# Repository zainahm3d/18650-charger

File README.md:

# 18650-charger
Dual channel USB-C LiFeP04 18650 charger based on 2x LTC4121 with two independant channels. Fully charged voltage is set to 3.6V at a current of 400mA.

## Images

## Test results from charging two cells
Capture from a Saleae logic analyzer. See the data file [here](doc/chargetest.sal)

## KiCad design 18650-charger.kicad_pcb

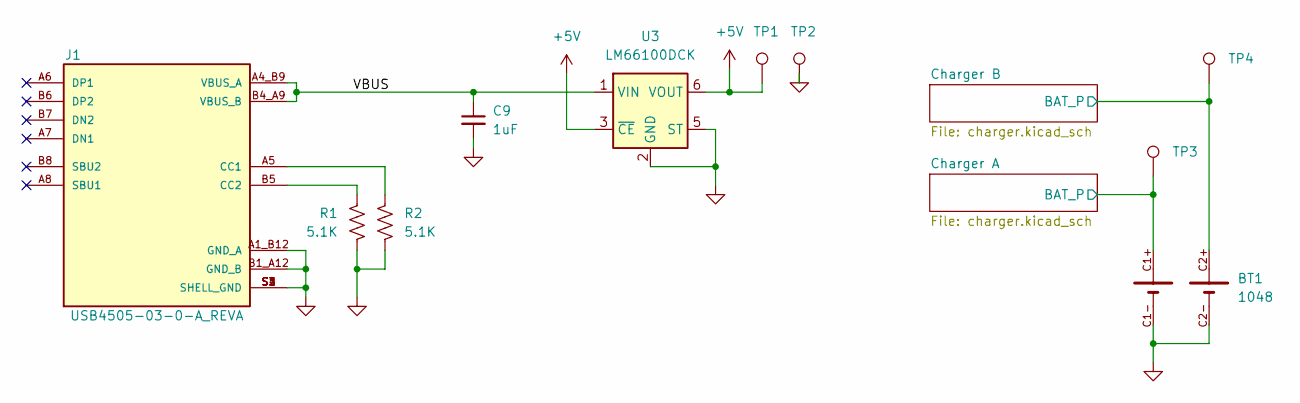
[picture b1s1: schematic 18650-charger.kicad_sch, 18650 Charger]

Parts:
BT1: 1048; BAT_1048
C9: 1uF; C_0402_1005Metric
J1: USB4505-03-0-A_REVA; GCT_USB4505-03-0-A_REVA; PARTREV A
R1, R2: 5.1K; R_0402_1005Metric
TP1, TP2, TP3, TP4: TestPoint; TP+195X110
U3: LM66100DCK; SOT-363_SC-70-6

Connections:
+5V: TP1.1, U3.3 (~CE), U3.6 (VOUT); also elsewhere on the board
/Charger A/BAT_P: BT1.C1+, TP3.1; also elsewhere on the board
/Charger B/BAT_P: BT1.C2+, TP4.1; also elsewhere on the board
/VBUS: C9.1, J1.A4_B9 (VBUS_A), J1.B4_A9 (VBUS_B), U3.1 (VIN)
GND: BT1.C1-, BT1.C2-, C9.2, J1.A1_B12 (GND_A), J1.B1_A12 (GND_B), J1.S1 (SHELL_GND), J1.S2 (SHELL_GND), J1.S3 (SHELL_GND), J1.S4 (SHELL_GND), R1.1, R2.2, TP2.1, U3.2 (GND), U3.5 (ST); also elsewhere on the board
unnamed: J1.A5 (CC1), R2.1
unnamed: J1.B5 (CC2), R1.2

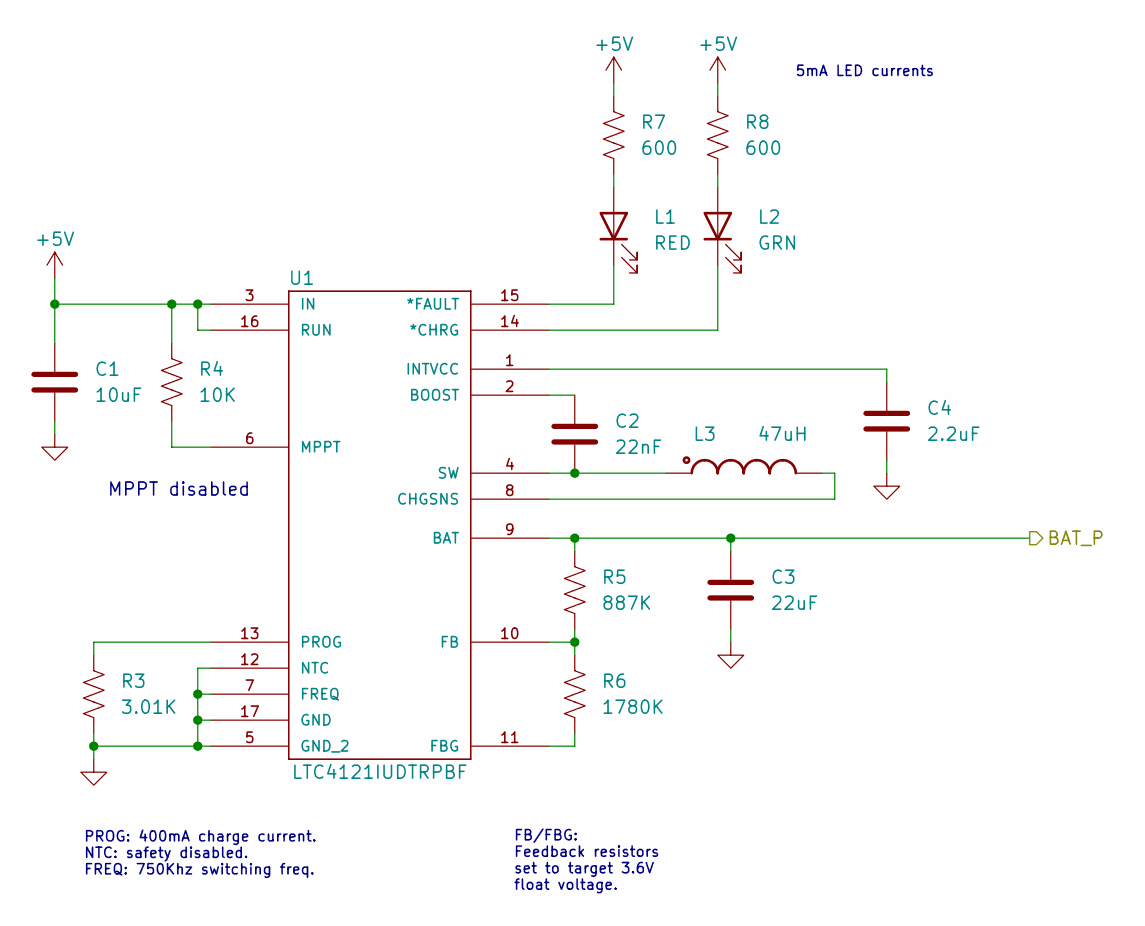
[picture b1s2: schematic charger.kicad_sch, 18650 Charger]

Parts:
C1: 10uF; C_1206_3216Metric
C2: 22nF; C_0402_1005Metric
C3: 22uF; C_0402_1005Metric
C4: 2.2uF; C_0402_1005Metric
L1: RED; LED_0603_1608Metric
L2: GRN; LED_0603_1608Metric
L3: 47uH; INDP_LPS4018-472MRB
R3: 3.01K; R_0402_1005Metric
R4: 10K; R_0402_1005Metric
R5: 887K; R_0402_1005Metric
R6: 1780K; R_0402_1005Metric
R7, R8: 600; R_0402_1005Metric
U1: LTC4121IUDTRPBF; QFN-16_UD; MANUFACTURER_PART_NUMBER ltc4121iud#trpbf

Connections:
+5V: C1.1, R4.1, R7.1, R8.1, U1.3 (IN), U1.16 (RUN); also elsewhere on the board
/Charger A/BAT_P: C3.1, R5.1, U1.9 (BAT); also elsewhere on the board
GND: C1.2, C3.2, C4.2, R3.1, U1.5 (GND_2), U1.7 (FREQ), U1.12 (NTC), U1.17 (GND); also elsewhere on the board
unnamed: L1.2 (A), R7.2
unnamed: L1.1 (K), U1.15 (*FAULT)
unnamed: L2.2 (A), R8.2
unnamed: L2.1 (K), U1.14 (*CHRG)
unnamed: C2.1, U1.2 (BOOST)
unnamed: L3.2, U1.8 (CHGSNS)
unnamed: R5.2, R6.1, U1.10 (FB)
unnamed: R6.2, U1.11 (FBG)
unnamed: C4.1, U1.1 (INTVCC)
unnamed: R4.2, U1.6 (MPPT)
unnamed: R3.2, U1.13 (PROG)
unnamed: C2.2, L3.1, U1.4 (SW)

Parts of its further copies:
C5: 10uF; C_1206_3216Metric
C6: 22nF; C_0402_1005Metric
C7: 22uF; C_0402_1005Metric
C8: 2.2uF; C_0402_1005Metric
L4: RED; LED_0603_1608Metric
L5: GRN; LED_0603_1608Metric
L6: 47uH; INDP_LPS4018-472MRB
R9: 3.01K; R_0402_1005Metric
R10: 10K; R_0402_1005Metric
R11: 887K; R_0402_1005Metric
R12: 1780K; R_0402_1005Metric
R13, R14: 600; R_0402_1005Metric
U2: LTC4121IUDTRPBF; QFN-16_UD; MANUFACTURER_PART_NUMBER ltc4121iud#trpbf

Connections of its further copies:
+5V: C5.1, R10.1, R13.1, R14.1, U2.3 (IN), U2.16 (RUN); also elsewhere on the board
/Charger B/BAT_P: C7.1, R11.1, U2.9 (BAT); also elsewhere on the board
GND: C5.2, C7.2, C8.2, R9.1, U2.5 (GND_2), U2.7 (FREQ), U2.12 (NTC), U2.17 (GND); also elsewhere on the board
unnamed: L4.2 (A), R13.2
unnamed: L4.1 (K), U2.15 (*FAULT)
unnamed: L5.2 (A), R14.2
unnamed: L5.1 (K), U2.14 (*CHRG)
unnamed: C6.1, U2.2 (BOOST)
unnamed: L6.2, U2.8 (CHGSNS)
unnamed: R11.2, R12.1, U2.10 (FB)
unnamed: R12.2, U2.11 (FBG)
unnamed: C8.1, U2.1 (INTVCC)
unnamed: R10.2, U2.6 (MPPT)
unnamed: R9.2, U2.13 (PROG)
unnamed: C6.2, L6.1, U2.4 (SW)

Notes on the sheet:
PROG: 400mA charge current. NTC: safety disabled. FREQ: 750Khz switching freq.
5mA LED currents
FB/FBG: Feedback resistors set to target 3.6V float voltage.
MPPT disabled

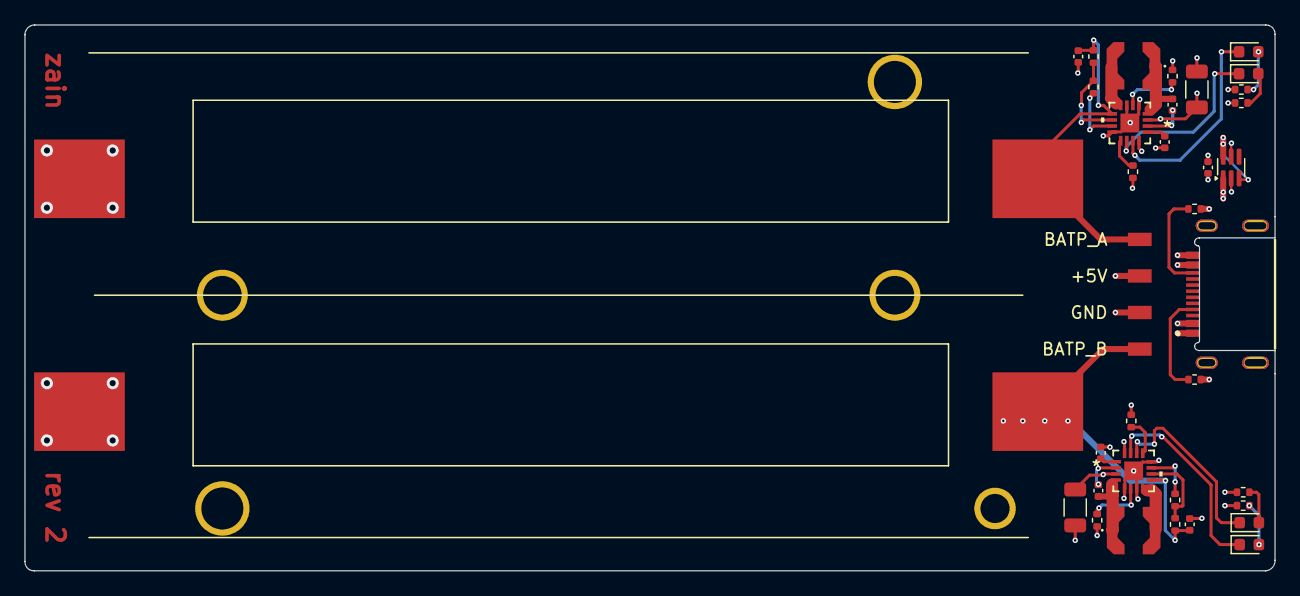
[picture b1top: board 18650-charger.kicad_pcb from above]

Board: 4 copper layers, 102.6 x 44.8 mm, 38 parts (0 on the bottom side), 31 nets.

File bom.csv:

Id;Designator;Package;Quantity;Designation;Digikey PN
1;TP2,TP3,TP1,TP4;TP+195X110;4;TestPoint;A106145CT-ND
2;J1;GCT_USB4505-03-0-A_REVA;1;USB4505-03-0-A_REVA;2073-USB4505-03-0-ACT-ND
3;R7,R8,R13,R14;R_0402_1005Metric;4;600;541-RCS0402604RFKEDCT-ND
4;R5,R11;R_0402_1005Metric;2;887K;YAG3251CT-ND
5;C5,C1;C_1206_3216Metric;2;10uF;490-6518-1-ND
6;L5,L2;LED_0603_1608Metric;2;GRN;732-12017-1-ND
7;R1,R2;R_0402_1005Metric;2;5.1K;YAG1457CT-ND
8;R4,R10;R_0402_1005Metric;2;10K;13-AA0402FR-0710KLCT-ND
9;L6,L3;INDP_LPS4018-473MRB;2;47uH;2457-LPS4018-473MRC-ND
10;C7,C3;C_0402_1005Metric;2;22uF;1276-7090-1-ND
11;C4,C8;C_0402_1005Metric;2;2.2uF;490-12267-1-ND
12;L4,L1;LED_0603_1608Metric;2;RED;732-12016-1-ND
13;U1,U2;QFN-16_UD;2;LTC4121IUDTRPBF;LTC4121EUD#PBF-ND
14;C6,C2;C_0402_1005Metric;2;22nF;399-17166-1-ND
15;R9,R3;R_0402_1005Metric;2;3.01K;13-RT0402FRE073KLCT-ND
16;R12,R6;R_0402_1005Metric;2;1780K;13-RC0402FR-071M78LCT-ND
17;BT1;BAT_1048;1;1048;36-1048-ND
18;U3;SOT-363_SC-70-6;1;LM66100DCK;296-53541-1-ND
19;C9;C_0402_1005Metric;1;1uF;399-12288-1-ND

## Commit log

2022-01-02 Version 1
2022-01-04 [WIP] Schematic updated with reverse blocking FETs
2026-01-04 Rev 2, add ideal diode
